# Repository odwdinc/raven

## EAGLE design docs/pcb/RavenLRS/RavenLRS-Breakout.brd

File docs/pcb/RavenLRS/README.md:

First test of costom pcb

RavenLRS breekout based off

ESP-WROOM-32 and SX1278 LoRa Module 433Mhz Ra-02

with support of optional lcd display.

4-18vDC

<a href="https://oshpark.com/shared_projects/5eDYOf5y"></img></a>

[embed]https://github.com/odwdinc/raven/blob/master/docs/pcb/RavenLRS/schmaptic.pdf[/embed]

BOM

<a href="https://www.tindie.com/products/ddebeer/esp-wroom-32/">1x ESP-WROOM-32</a>

<a href="https://www.makerfabs.com/index.php?route=product/product&product_id=409">1x RA-02 by ai thinker</a>

<a href="https://www.makerfabs.com/index.php?route=product/product&product_id=437">1x 433MHz Spring Antenna</a>

<a href="https://www.mouser.com/ProductDetail/863-2N7002ET1G">1x 2N7002ET1G MOSFET NFET SOT23 60V 310mA 2.5Ohms</a>

<a href="https://www.mouser.com/ProductDetail/506-FSMSM">2x FSMSM Tactile Switche</a>

<a href="https://www.mouser.com/ProductDetail/78-1N4148WS-E3-18">2x 1N4148WS-E3-18	Diode</a>

<a href="https://www.mouser.com/ProductDetail/755-ESR03EZPJ103">2x 	ESR03EZPJ103 Thick Film Resistor 0603 10Kohm</a>

<a href="https://www.mouser.com/ProductDetail/511-LDL1117S33R">1x 	LDL1117S33R LDO Voltage Regulator 3.3v</a>

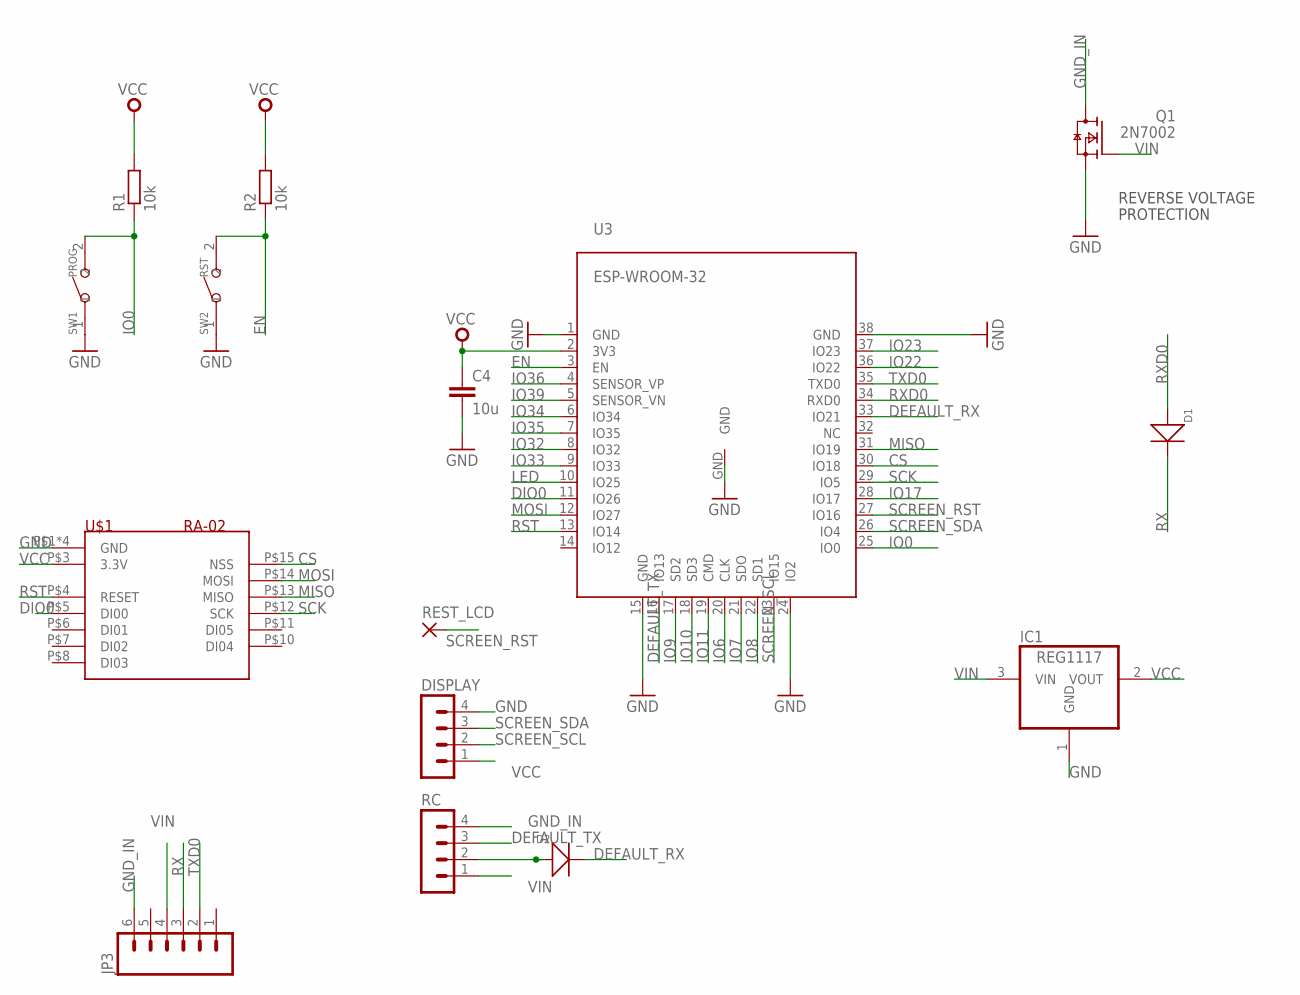
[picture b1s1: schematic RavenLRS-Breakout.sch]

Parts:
C4: 10u; C0603
D1, D2: DIODE'0805'; SOD-323
DISPLAY: MA04-1
IC1: REG1117; SOT223
JP3: M06SILK_FEMALE_PTH; 1X06
Q1: 2N7002; SOT23
R1, R2: 10k; R0603
RC: MA04-1
REST_LCD: SMD2; SMD1,27-2,54
SW1: PROG; SW2-4.0-6.0X3.0X2.5MM
SW2: RST; SW2-4.0-6.0X3.0X2.5MM
U3: ESP-WROOM-32
U$1: RA-02

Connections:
CS: U3.30 (IO18), U$1.P$15 (NSS)
DEFAULT_RX: D2.-, U3.33 (IO21)
DEFAULT_TX: RC.3, U3.16 (IO13)
DIO0: U3.11 (IO26), U$1.P$5 (DI00)
EN: R2.1, SW2.2, U3.3 (EN)
GND: C4.2, DISPLAY.4, IC1.1 (GND), Q1.2 (S), SW1.1, SW2.1, U3.1 (GND), U3.15 (GND), U3.24 (IO2), U3.38 (GND), U3.GND, U$1.P$1 (GND), U$1.P$2 (GND), U$1.P$9 (GND), U$1.P$16 (GND)
GND_IN: JP3.6, Q1.3 (D), RC.4
IO0: R1.1, SW1.2, U3.25 (IO0)
IO6: U3.20 (CLK)
IO7: U3.21 (SDO)
IO8: U3.22 (SD1)
IO9: U3.17 (SD2)
IO10: U3.18 (SD3)
IO11: U3.19 (CMD)
IO17: U3.28 (IO17)
IO22: U3.36 (IO22)
IO23: U3.37 (IO23)
IO32: U3.8 (IO32)
IO33: U3.9 (IO33)
IO34: U3.6 (IO34)
IO35: U3.7 (IO35)
IO36: U3.4 (SENSOR_VP)
IO39: U3.5 (SENSOR_VN)
LED: U3.10 (IO25)
MISO: U3.31 (IO19), U$1.P$13 (MISO)
MOSI: U3.12 (IO27), U$1.P$14 (MOSI)
unnamed: D2.+, RC.2
RST: U3.13 (IO14), U$1.P$4 (RESET)
RX: D1.-, JP3.3
RXD0: D1.+, U3.34 (RXD0)
SCK: U3.29 (IO5), U$1.P$12 (SCK)
SCREEN_RST: REST_LCD.1, U3.27 (IO16)
SCREEN_SCL: DISPLAY.2, U3.23 (IO15)
SCREEN_SDA: DISPLAY.3, U3.26 (IO4)
TXD0: JP3.2, U3.35 (TXD0)
VCC: C4.1, DISPLAY.1, IC1.2 (VOUT), R1.2, R2.2, U3.2 (3V3), U$1.P$3 (3.3V)
VIN: IC1.3 (VIN), JP3.4, Q1.1 (G), RC.1

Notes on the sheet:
REVERSE VOLTAGE
PROTECTION

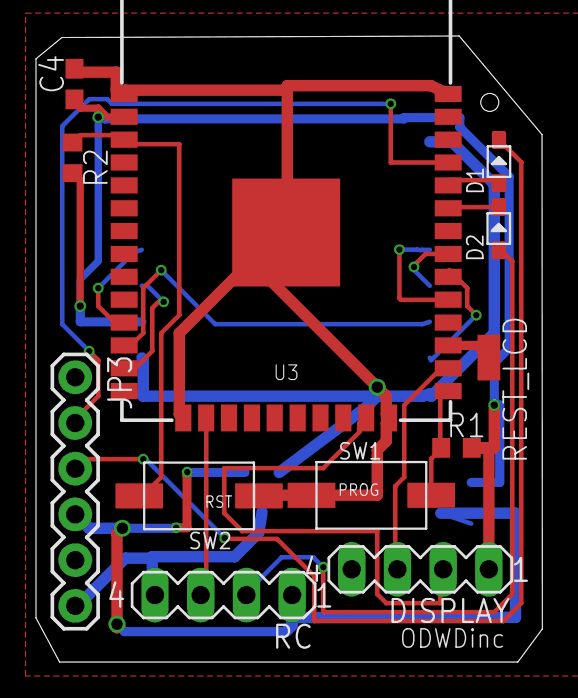
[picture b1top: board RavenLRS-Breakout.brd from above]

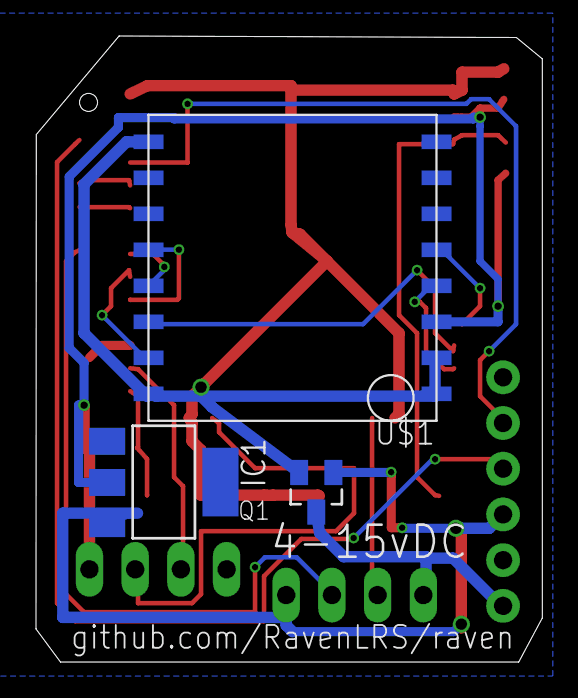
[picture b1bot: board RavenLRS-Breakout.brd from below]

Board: 2 copper layers, 28.1 x 34.8 mm, 15 parts (3 on the bottom side), 21 nets.

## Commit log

2018-09-05 First test of costom pcb
    RavenLRS breekout based off
    ESP-WROOM-32
    RA-02 by ai thinker
    with support of optional lcd display.
2018-09-05 Created README.md
2018-09-05 added oshpark.com link
2018-09-05 board images
2018-09-05 Added Images, links, and BOM
2018-09-05 added schmaptic

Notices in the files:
parts and their libraries:
SparkFun-Connectors: Licensing: Creative Commons ShareAlike 4.0 International - https://creativecommons.org/licenses/by-sa/4.0
